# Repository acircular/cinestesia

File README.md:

# cinestesia
Repositorio del proyecto de danza y tecnología "Cinestesia : dispositivos para una algoritmia del cuerpo"

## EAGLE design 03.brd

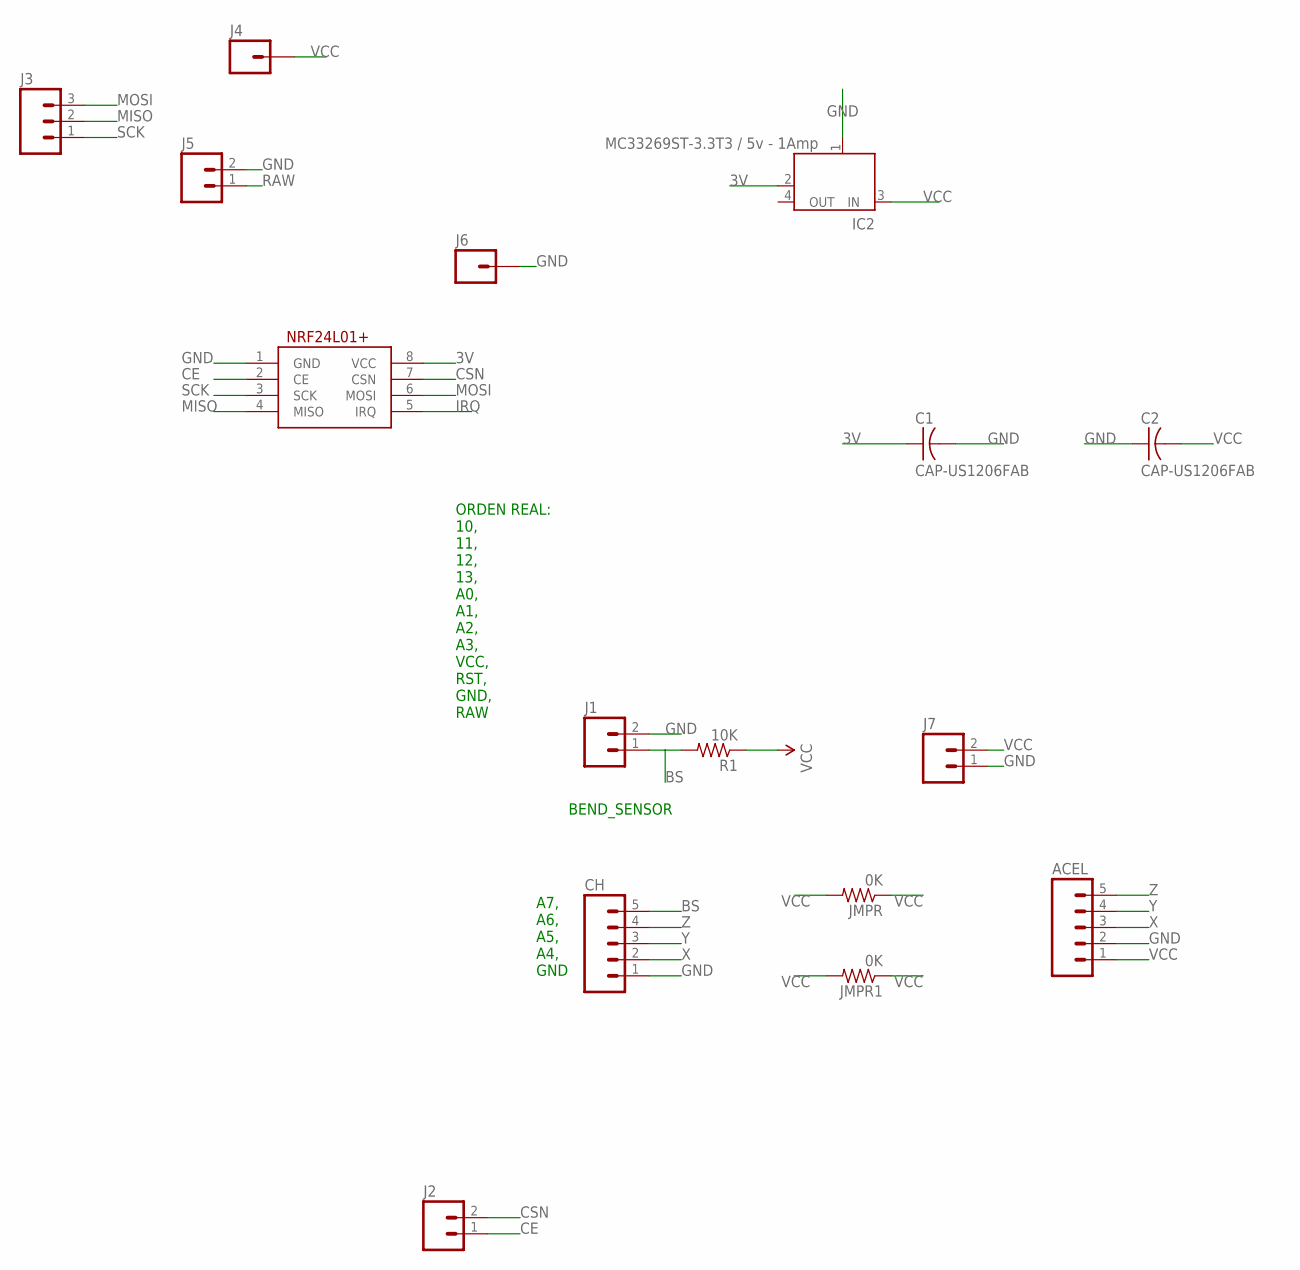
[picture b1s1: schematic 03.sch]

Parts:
ACEL: M05NO_SILK; 1X05_NO_SILK
C1, C2: CAP-US1206FAB; C1206FAB
CH: M05NO_SILK; 1X05_NO_SILK
IC2: MC33269ST-3.3T3 / 5v - 1Amp; SOT223
J1, J2, J5: M021X02_NO_SILK; 1X02_NO_SILK
J3: M031X03_NO_SILK; 1X03_NO_SILK
J4: M01NOSILK-KIT; 1X01NS-KIT
J6: M01PTH_NO_SILK_YES_STOP; 1X01_NO_SILK
J7: M023.5MM; SCREWTERMINAL-3.5MM-2
JMPR, JMPR1: 0K; R1206FAB
NRF24L01+: NRF24L01+; 2X04_THRU
R1: 10K; R1206FAB

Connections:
3V: C1.1, IC2.2 (OUT), NRF24L01+.8 (VCC)
BS: CH.5, J1.1, R1.2
CE: J2.1, NRF24L01+.2 (CE)
CSN: J2.2, NRF24L01+.7 (CSN)
GND: ACEL.2, C1.2, C2.1, CH.1, IC2.1 (GND/ADJ), J1.2, J5.2, J6.1, J7.1, NRF24L01+.1 (GND)
IRQ: NRF24L01+.5 (IRQ)
MISO: J3.2, NRF24L01+.4 (MISO)
MOSI: J3.3, NRF24L01+.6 (MOSI)
RAW: J5.1
SCK: J3.1, NRF24L01+.3 (SCK)
VCC: ACEL.1, C2.2, IC2.3 (IN), J4.1, J7.2, JMPR.1, JMPR.2, JMPR1.1, JMPR1.2, R1.1
X: ACEL.3, CH.2
Y: ACEL.4, CH.3
Z: ACEL.5, CH.4

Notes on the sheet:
ORDEN REAL: 10, 11, 12, 13, A0, A1, A2, A3, VCC, RST, GND, RAW
A7, A6, A5, A4, GND
BEND_SENSOR

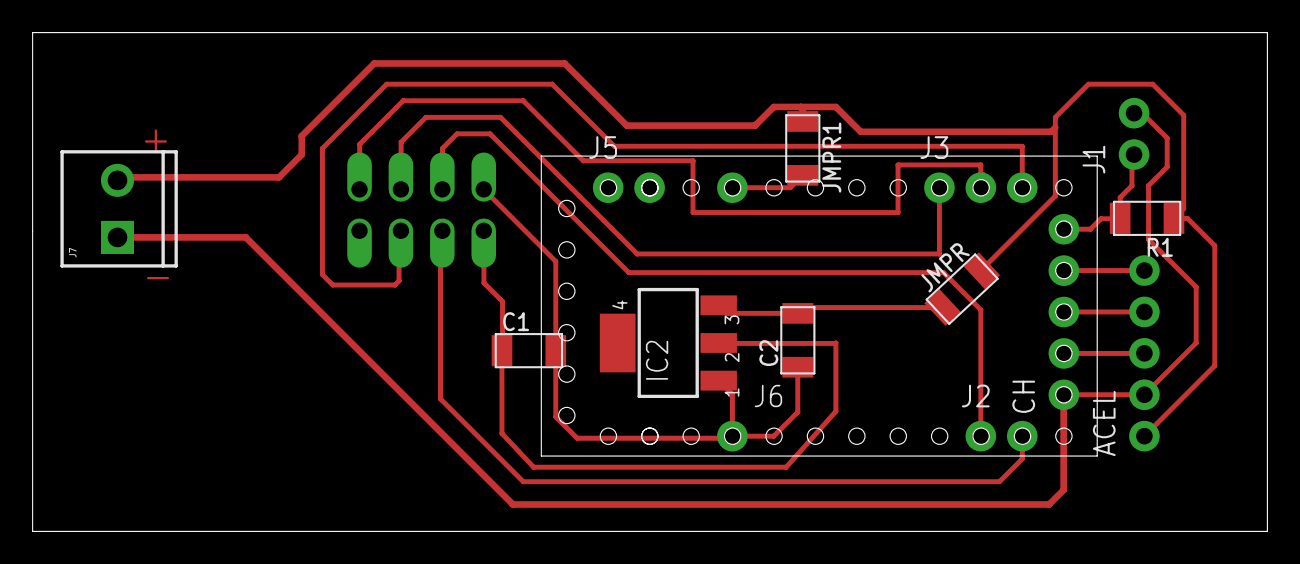
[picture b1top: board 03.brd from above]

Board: 2 copper layers, 75.7 x 30.6 mm, 16 parts (0 on the bottom side), 12 nets.

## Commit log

2016-10-20 Probando las librerias de arduino (RF24, RF24 Network, RF24 Mesh para la comunicación en malla y transmisión de los datos de los sensores
2016-10-20 Rename RF24Mesh_Example_Master_pines9y10.ino to NODOS/RF24Mesh_Example_Master_pines9y10.ino
2016-10-20 Rename RF24Mesh_acelerometro_esclavo.ino to NODOS/RF24Mesh_acelerometro_esclavo.ino
2016-10-20 Rename RF24Mesh_gy521.ino to NODOS/RF24Mesh_gy521.ino

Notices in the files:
parts and their libraries:
SparkFun-Connectors: Licensing: Creative Commons ShareAlike 4.0 International - https://creativecommons.org/licenses/by-sa/4.0
